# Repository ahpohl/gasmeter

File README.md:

# Overview

This project is about reading the counter of [diaphragm gas volume meter](https://en.wikipedia.org/wiki/Gas_meter) which is commonly installed in residential properties to count and bill the consumed gas. The last dial of the meter has a reflective sticker, which can be utilised to detect a full revolution of the dial.

In some meters the reflective sticker is made from a magnetic material and a very sensitive magnetometer is sufficient to detect the changes in the earth magnetic field when the sticker passes by the sensor. In the first version of this project used the [SparkFun 3-axis magnetometer](https://www.sparkfun.com/products/retired/12670) to detect a full revolution of the .001 m³ digit wheel. Since my gas meter was replaced with a new non-magnetic version, the magenetometer sensor doesn't work anymore.

Here I describe a new sensor device, which uses an infrared LED and a phototransistor to detect the changes in reflectivity when the reflective sticker on the last dial passes by the phototransitor. The measurement principle was inspired by the [pulsemeter](https://github.com/ahpohl/pulsemeter) and the device looks like this when mounted in front of the gas meter:

The schematics, board layout and part list of the gasmeter dongle hardware is described in more detail in the [Gasmeter wiki](https://github.com/ahpohl/gasmeter/wiki).

On the software side, the Gasmeter program reads the current gas volume from the meter and forwards it to a MQTT broker on the network. The data is stored in a TimescaleDB database and visualised on a Grafana dashboard. The installation of the software stack, including the setup and maintainance of the database, is described on the [Smartmeter](https://github.com/ahpohl/smartmeter/wiki) wiki pages.

## Build instructions

To compile Gasmeter from source, a Makefile for (cross-)compilation is provided:

```
make CROSS_COMPILE=aarch64-unknown-linux-gnu
make install
```

Alternatively, there is also an Arch Linux package called [gasmeter](https://aur.archlinux.org/packages/gasmeter) published in the AUR.

The hardware dongle needs firmware for the Atmel microcontroller in order to communicate with the gasmeter program. To compile the firmware, first install the AVR toolchain through your package manager. On Arch Linux, install `avr-gcc` and `avr-libc` packages and then `make upload` to compile and upload the firwmare. On a new microcontroller, a bootloader needs to be flashed first to accept a firmware image via upload. The preparation of a new µC is described in the [wiki](https://github.com/ahpohl/gasmeter/wiki).

## Installation

The Arch Linux package provides a systemd service file and installs the configuration file in `/etc/gasmeter/gasmeter.conf`. The service can be started with:

```
systemctl start gasmeter
```

When building directly from source, the daemon can be directly started with:

```
gasmeter --config resources/config/gasmeter_example.conf

```

## Run in Docker

The Arch Linux package installs a docker compose in `/etc/gasmeter/docker-compose.yaml` and a `Dockerfile`. Alternatively, these files are also in the root folder or the source. Before building and starting the container, the serial device used by the gasmeter hardware needs to be set in `docker-compose.yaml` in addtion to `gasmeter.conf` to give Docker access to the device.

```
docker-compose up --build
```

## Configuration

The Gasmeter program is configured with a configuration file located in `/etc/gasmeter/gasmeter.conf`. At least the serial device of the hardware, the MQTT hostname and topic to publish to needs to be set. Optionally, Gasmeter supports MQTT password authentication and TLS connection encryption. Finally, the gas tariff, which consists price per kWh, a yearly service charge and the gas conversion factor (found on the last bill), needs to be set here for the current bill to be shown on the dashboard.

On first run, the low and high threshold parameters need to be determined. For this, there is a special `raw_mode` option in the config file, which outputs the raw sensor values to the console. To record values create a log file with:

```
gasmeter --config gasmeter.conf | tee raw_values.log
```

Plotting the raw values gives a diagram like this (the gnuplot script is provided in the resources folder):

```
gnuplot < sensor.gnuplot > threshold_levels.png
```

The threshold level low needs to be set slightly above the baseline and level high below the maximum of the raw value. The larger the difference between the baseline and the maximum, the better the tolerance against noise and variations in reflected light intensity. Here the baseline is around 600 and the maximum at 950-1000 and a low level of 750 and high level of 900 works well.

A minimal `gasmeter.conf` config file looks like this:

```
serial_device /dev/ttyUSB0
mqtt_broker localhost
mqtt_topic gasmeter
gas_rate 261.80
gas_price 0.0583
gas_factor 10.835
level_low 750
level_high 900
```

## JSON output

Example JSON published by Gasmeter in the `gasmeter/live` topic:

```
{
  "time":1730287096822, # timestamp, secs since epoch
  "volume":4207.18,     # gas volume, m³ 
  "state":0,            # detection of volume change
  "rate":235.40,        # yearly service rate
  "price":0.1042,       # price per kWh, € (or whatever)
  "factor":11.048       # gas conversion factor, kWh*m³
}
```

## Future development

* Replace the host running gasmeter with an ESP32 version mounted directly on the PCB
* Web interface with MQTT and firmware download capability
* ESP32 version inspired by [AI-on-the-edge](https://github.com/jomjol/AI-on-the-edge-device) and the [Opentherm gateway](https://www.nodo-shop.nl/en/featured/211-opentherm-gateway.html)

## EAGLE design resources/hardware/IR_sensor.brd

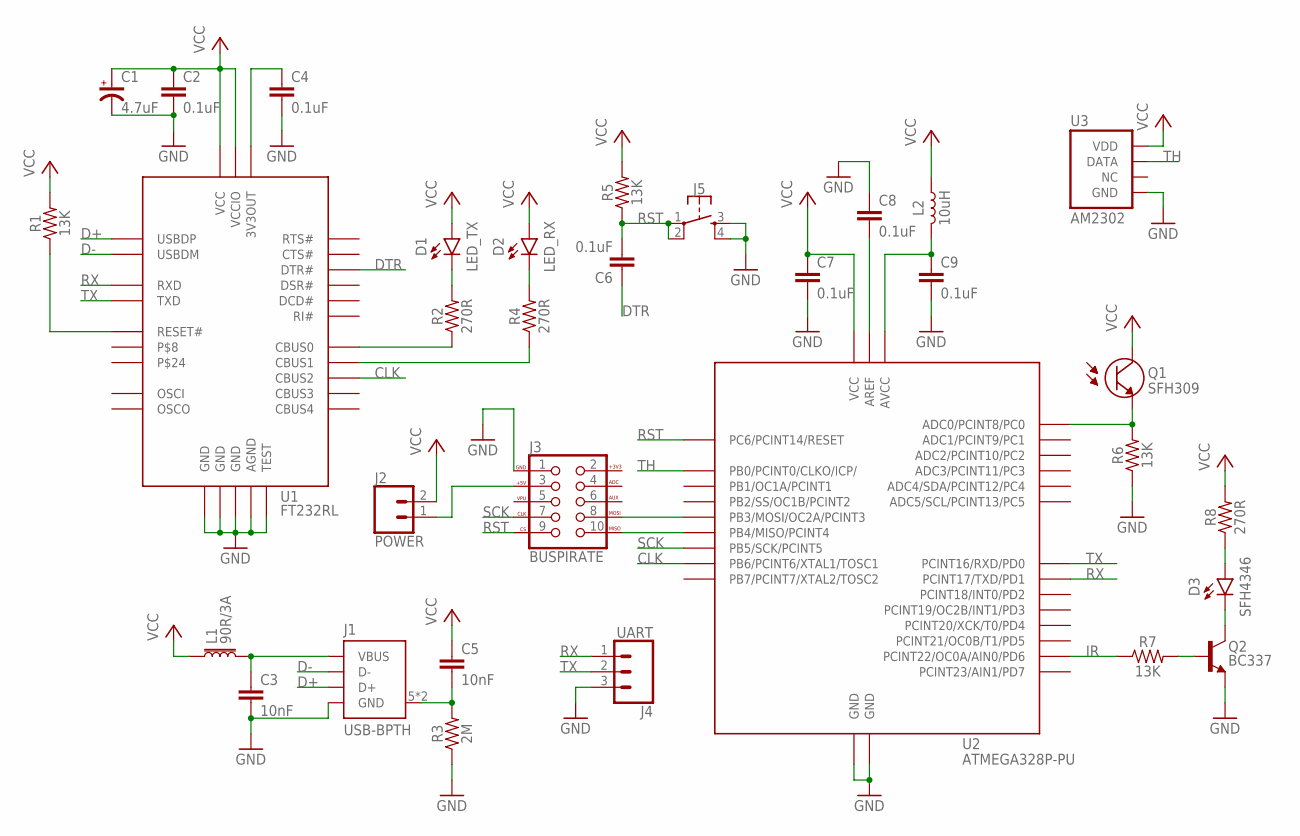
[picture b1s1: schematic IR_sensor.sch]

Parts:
C1: 4.7uF; CPOL-RADIAL-2.5MM-5MM
C2, C4, C6, C7, C8, C9: 0.1uF; CAP-PTH-5MM
C3: 10nF; CAP-PTH-2.5MM
C5: 10nF; CAP-PTH-5MM
D1: LED_TX; LED_5MM
D2: LED_RX; LED_5MM
D3: SFH4346; LED_3MM_R
J1: USB-BPTH; USB-B-PTH
J2: POWER; 1X02
J3: BUSPIRATE; 2X5-SHROUDED
J4: UART; 1X03
J5: SWITCH; TACTILE_SWITCH_PTH_6.0MM
L1: 90R/3A; AXIAL-0.3
L2: 10uH; AXIAL-0.4
Q1: SFH309; LED_3MM_R
Q2: BC337; TO-92
R1, R5, R6, R7: 13K; AXIAL-0.3
R2, R4, R8: 270R; AXIAL-0.3
R3: 2M; AXIAL-0.3
U1: FT232RL; TSSOP-28-BL
U2: ATMEGA328P-PU; DIP28
U3: AM2302; SNR4-2.54

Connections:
+3V3: J3.2 (+3V3)
ADC: Q1.A (E), R6.P$2 (2), U2.23 (ADC0/PCINT8/PC0)
CLK: U1.13 (CBUS2), U2.9 (PB6/PCINT6/XTAL1/TOSC1)
D+: J1.3 (D+), U1.15 (USBDP)
D-: J1.2 (D-), U1.16 (USBDM)
DTR: C6.1, U1.2 (DTR#)
GND: C1.2 (-), C2.2, C3.2, C4.2, C7.2, C8.1, C9.2, J1.4 (GND), J3.1 (GND), J4.3, J5.3, J5.4, Q2.1 (E), R3.P$1 (1), R6.P$1 (1), U1.7 (GND), U1.18 (GND), U1.21 (GND), U1.25 (AGND), U1.26 (TEST), U2.8 (GND), U2.22 (GND), U3.P$4 (GND)
IR: R7.P$1 (1), U2.12 (PCINT22/OC0A/AIN0/PD6)
MISO: J3.10 (MISO), U2.18 (PB4/MISO/PCINT4)
MOSI: J3.8 (MOSI), U2.17 (PB3/MOSI/OC2A/PCINT3)
unnamed: C3.1, J1.1 (VBUS), L1.P$2 (2)
unnamed: R1.P$1 (1), U1.19 (RESET#)
unnamed: C4.1, U1.17 (3V3OUT)
unnamed: D1.K, R2.P$2 (2)
unnamed: C8.2, U2.21 (AREF)
unnamed: D2.K, R4.P$2 (2)
unnamed: J2.1, J3.3 (+5V)
unnamed: D3.K, Q2.3 (C)
unnamed: R2.P$1 (1), U1.23 (CBUS0)
unnamed: C5.2, J1.5 (SHIELD), J1.6 (SHIELD), R3.P$2 (2)
unnamed: D3.A, R8.P$1 (1)
unnamed: Q2.2 (B), R7.P$2 (2)
unnamed: C9.1, L2.P$2 (2), U2.20 (AVCC)
unnamed: R4.P$1 (1), U1.22 (CBUS1)
RST: C6.2, J3.9 (CS), J5.1, J5.2, R5.P$1 (1), U2.1 (PC6/PCINT14/RESET)
RX: J4.1, U1.5 (RXD), U2.3 (PCINT17/TXD/PD1)
SCK: J3.7 (CLK), U2.19 (PB5/SCK/PCINT5)
TH: U2.14 (PB0/PCINT0/CLKO/ICP/), U3.P$2 (DATA)
TX: J4.2, U1.1 (TXD), U2.2 (PCINT16/RXD/PD0)
VCC: C1.1 (+), C2.1, C5.1, C7.1, D1.A, D2.A, J2.2, L1.P$1 (1), L2.P$1 (1), Q1.K (C), R1.P$2 (2), R5.P$2 (2), R8.P$2 (2), U1.4 (VCCIO), U1.20 (VCC), U2.7 (VCC), U3.P$1 (VDD)

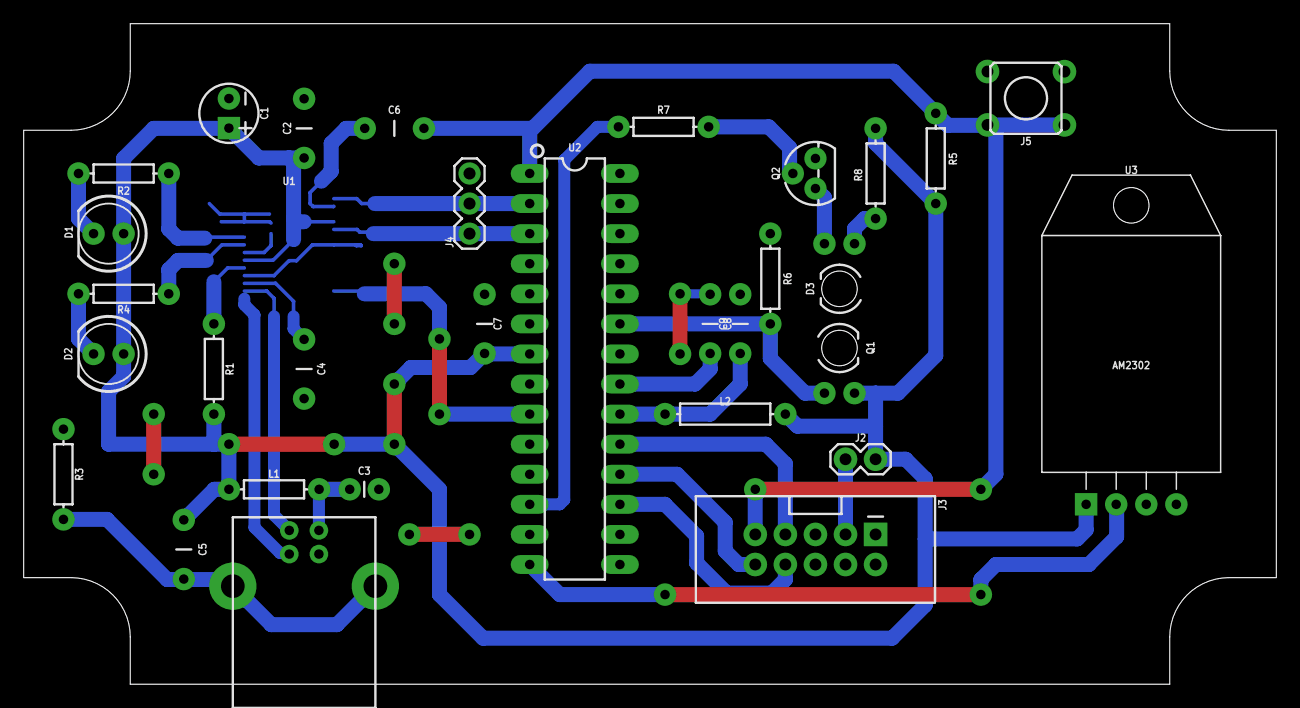
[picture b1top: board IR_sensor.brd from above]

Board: 2 copper layers, 105.8 x 55.8 mm, 32 parts (0 on the bottom side), 29 nets.

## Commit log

2019-10-14 verify all bitmanipulations
2019-10-14 add getDR_OS function
2019-10-14 fix return value of getDR_OS()
2019-10-14 gitignore dependencies
2019-10-14 get dros in main
2019-10-14 setting data rate does not work
2019-10-15 remove m_isActive and m_isRaw private members
2019-10-15 add delay function
2019-10-15 run uncalibrated
2019-10-16 added delays in library
2019-10-17 change delay function, needs tested
2019-10-17 fix delay bug
2019-10-18 get delay
2019-10-18 major function cleanup
2019-10-18 introduced some bugs during function cleanup
2019-10-19 setOffset negative bug
2019-10-19 offset not negative, signed bit bug
2019-10-20 get offset signed bit error
2019-10-20 get offset fixed
2019-10-20 play polling, active, trigger and delay
2019-10-21 add getMagPoll function
2019-10-22 put mag3110 into own library project
2019-10-22 compile static
2019-11-26 use mag3110 library, basic recording
2019-12-01 gasmeter ready for rrdtool
2019-12-01 gasmeter framework copied from pulsemeter
2019-12-01 Makefile build directory
2019-12-01 update gitignore
2019-12-07 inherited mag3110 methods
2019-12-07 setup interrupt and open i2c device
2019-12-07 output magnetic field working
2019-12-08 magnetic field as private member
2019-12-08 write raw magnetic field to rrd works
2019-12-08 added systemd service and conf file
2019-12-08 created rrd counter database
2019-12-08 rrd counter methods created, not tested
2019-12-09 detect counter increase, needs testing
2019-12-10 level and hysteris mandatory parameters
2019-12-10 gasmeter completed
2020-02-01 fix syntax error in rrd schema
2020-02-01 minor changes
2020-02-01 major code rewrite
2020-02-02 no compile errors
2020-02-02 rrdcached socket not found
2020-02-02 protect m_counter with mutex lock
2020-02-02 new setMeterReading function
2020-02-02 bug: gas counter not updating in rrd
2020-02-02 remove mutex lock_guards
2020-02-02 add obis constants
2020-02-02 write obis code function added
2020-02-03 add factor and ramdisk parameterw
2020-02-04 fix compile errors
2020-02-04 obis output complete
2020-02-06 fix Makefile install target
2020-02-06 run as a service
2020-02-07 remove wiringpi, disable interrupt
2020-06-07 initial libgpiod rising edge callback
2020-06-08 add gpiochip and offset arguments
2020-06-09 libgpiod event polling works
2020-06-09 moved setup of libgpiod into own function
2020-06-09 update gasmeter.conf and service file
2020-06-09 rrd and socket strncpy const build error
2020-06-09 rename gpiochip to chip argument
2020-08-13 add MQTT publish
2020-08-13 publish MQTT magnetization
2020-08-13 fix calculation of volume
2020-08-14 change energy topic to gas_energy
2020-08-21 add mqtt json output
2020-08-21 read mag3110 @2.5Hz, mqtt @2Hz, rrd @300s
2020-08-21 enable mqtt output
2020-08-21 fix rrd minimum one second step error
2020-08-21 add mqtt tags level, hyst and step size
2020-08-21 remove std namespace
2020-08-22 add influxdb insert statements
2020-08-23 add grafana dashboard
2020-08-24 add tariff info
2020-08-24 edit service and conf file
2020-08-24 make conversion factor optional
2020-08-24 add gas tariff details to config file
2020-08-29 edited mqtt.cpp
2020-08-29 add node red flow
2020-09-04 fix influxdb daily continuous query
2020-09-13 update dashboard
2021-08-01 take solarmeter files and rename
2021-08-01 copy libabbaurora files into project
2021-08-04 edit postgres schema
2021-08-04 gasmeter schema
2021-08-05 fix most compiler errors
2021-08-05 copy from libabbaurora
2021-08-05 edit gasmeter firmware
2021-08-05 fix compiler errors
2021-08-06 add eagle schematics and cam files
2021-08-06 removed most firmware functions
2021-08-06 edit datagram
2021-08-06 first attempt at new gasmeter control
2021-08-07 fix typo in gasmeter.sql script
2021-08-07 adapt communication protocol
2021-08-07 add send volume function
2021-08-07 correct gas key formatting in config file
2021-08-08 receive values every five seconds
2021-08-10 added avr firmware
2021-08-18 start implementing firmware
2021-08-18 change baudrate to B9600
2021-08-19 send packet ok
2021-08-19 basic packet processing
2021-08-19 echo sent and received packets
2021-08-21 command send receive working
2021-08-21 adjust serial timeout
2021-08-22 save mess
2021-08-22 report uart error codes
2021-08-22 disable hupcl modem reset after hangup
2021-08-22 add millis timer
2021-08-22 wait for reset of avr on first connect
2021-08-22 measure temp/humid immedately after startup
2021-08-22 transfer singed int failed
2021-08-22 need to convert endianess
2021-08-22 byte order confusion
2021-08-23 fixed endianess
2021-08-24 read dht sensor payload
2021-08-24 dht22 sensor working
2021-08-24 check dht timing
2021-08-24 fix nodejs and gasmeter postgres table
2021-08-25 set logging framework
2021-08-25 log level config key working
2021-08-25 make log level optional
2021-08-26 config validate keys earlier
2021-08-26 fix segfault config no value
2021-08-28 send adc value, gnuplot sensor.plot
2021-09-03 set level thresholds
2021-09-03 use fast PWM
2021-09-04 send adc value using millis timer
2021-09-04 delay ADC start until signal is stable
2021-09-04 IR led PWM 10 % duty cycle
2021-09-04 implement simple gas meter readout
2021-09-04 no raw adc output
2021-09-04 fixed adc raw output
2021-09-05 remove merge conflict
2021-09-05 change counting else if
2021-09-05 modify counting algo
2021-09-07 edit sql tables
2021-09-08 update grafana dashboard and node red flow
2021-09-10 update node red and grafana flows
2021-09-10 add raw debug
2021-09-10 moved program loop to separate function
2021-09-15 fast raw output mode for debugging
2021-09-16 gnuplot show raw and volume
2021-09-16 wait before reading next adc value
2021-09-16 change baud rate to 57600 baud
2021-09-17 adjust intercharacter delay
2021-09-19 gasmeter is counting too fast
2021-09-20 removed commented code
2021-10-06 disable dht22
2021-10-06 enable publishing
2021-10-06 publish every 5 seconds
2021-10-07 set baudrate to 19200 baud
2021-11-04 get log level in main
2021-11-05 remove all ready flags
2021-11-05 counter correct, but don't know why
2021-11-05 remove adc ready flag, counts working
2021-11-05 move counter eval to adc isr
2021-11-05 remove comp timer A interrupt
2021-11-05 initialze gasmeter struct with defaults
2021-11-06 fast raw log
2021-11-06 restore normal mode
2021-11-06 use ADC prescaler CLK/128 93.5 kHz
2021-11-06 make gasmeter volatile
2021-11-06 disbable global interrupts
2021-11-06 add adc_value to gasmeter struct
2021-11-06 disable ADC interrupt when accessing gasmeter
2021-11-07 send raw includes hysteresis
2021-11-07 fixed theshold level bug
2021-11-08 add eeprom code, not tested
2021-11-08 update eeprom instead of write
2021-11-08 Revert "update eeprom instead of write"
    This reverts commit 7ea6cabdc72cd090f58773e36a6eabbb8c77c535.
2021-11-08 save gas volume to eeprom
2021-11-08 fix daily bill calculation
2021-11-09 save trigger levels in eeprom
2021-11-09 remove gasmeter struct default initialistion
2021-11-13 makefile for gasmeter upload
2021-11-14 clear volume command
2021-11-14 clear gasmeter command
2021-11-14 transmission error
2021-11-14 update config file
2021-11-14 add optional counter led
2021-11-14 disable counter led
2021-11-16 sink current for counter led
2022-01-03 add readme and changelog
2022-01-03 update changelog
2022-01-04 cast volume to signed int
2022-01-05 update example config file
2022-01-05 collected ir.log with raw
2022-01-08 pg: use experimental time bucket function
2022-02-02 add unique constraint on archive bucket_1d
2022-02-02 add where clause in daily_view
2022-02-03 add unique indices for mat view refresh concurrently
2022-03-30 add flame_on json output
2022-03-30 alter gasmeter table: add flame_on column
2022-03-30 update node flow and grafana
2022-03-30 separate get state function
2022-03-31 increase main thread wait to 60 seconds
2022-04-01 remove dht code
2022-04-01 remove dht temp and humidiy
2022-04-01 remove temp and humidity from database
2022-04-01 alter gasmter live table
2022-04-01 remove gasmeter strings class
2022-04-01 use condtion variables and threads in main
2022-04-02 lambda function cleanup
2022-04-02 clean up worker thread
2022-04-02 remove thread vector
2022-04-06 add averages to montly view
2022-04-06 update grafana dashboard
2022-10-29 output current meter reading
2022-11-02 create atmel and espressif folders
2022-11-02 initialise new espressif project
2022-11-02 create gasmeter project from scratch
2022-11-03 add platformio project
2022-11-03 remove platformio project
2022-11-04 add vscode project files
2022-11-04 add openocd debug config
2022-11-04 ADC2 together with wifi (not possible)
2022-11-04 put wifi into separate header file
2022-11-04 move atmel firmware folder
2022-11-04 added adc header and impl
2022-11-04 added mqtt header and source
2022-11-04 add ledc header and source
2022-11-05 set gpio adc and ledc
2022-12-29 updated mqtt publish
2022-12-29 add mqtt notify online flag
2022-12-29 main loop publish before wait
2023-02-14 updated retention policies
2023-03-24 remove outer array in json output
2023-03-24 commit latest changes
2023-03-24 remove array in node-red flow
2023-04-10 remove time_bucket experimental
2023-04-15 time buckets with local time zone
2023-04-15 update monthly plot grafana dashboard
2023-07-22 plpgsql function to calc percentages
2023-08-30 update retention policies
2023-11-07 grant select to nodejs
2024-02-13 fix day error in trend calc
2024-10-20 apply clang-format llvm
2024-10-20 apply clang-format llvm to firmware
2024-10-28 logging reduced to enable/disable in classes
2024-10-28 remove gasmeter enum header
2024-10-28 serial and raw logging broken
2024-10-28 add raw mode config option
2024-10-28 remove log from GasmeterSerial class
2024-10-28 serial log moved to GasmeterFirmware
2024-10-28 print send while logging
2024-10-28 receive raw only in RawMode
2024-10-28 add firmware target to Makefile
2024-10-28 add upload target
2024-10-30 update gitignore, upload png
2024-10-30 sensor.gnuplot set precision
2024-10-30 new release
2024-10-30 fix typo in readme
2024-10-30 update threshold levels image
2024-10-30 remove volume from raw value plot
2024-11-10 fix mqtt port config error
